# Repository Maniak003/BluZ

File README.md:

<!DOCTYPE html>
<html lang="en" data-color-mode="auto" data-light-theme="light" data-dark-theme="dark">
  <head>
    <meta charset="utf-8">
  </head>
    <body class="logged-in env-production page-responsive page-blob" style="word-wrap: break-word;">
      <p> BluZ Scintillation gamma spectrometer based on SiPM Sensl FC60035/FJ60035, Broadcom AFBR-S4N66C013, EQR15 11-6060D-S & NaI(Tl) or SrI2(Eu). Bluetooth 5.x<br>For discussion https://t.me/+mRf25RTZtPs3NTli</p>
      <a href=https://github.com/Maniak003/BluZ/releases/download/BluZ/BluZ-release.apk> Application in release </a>

    </body>
</html>

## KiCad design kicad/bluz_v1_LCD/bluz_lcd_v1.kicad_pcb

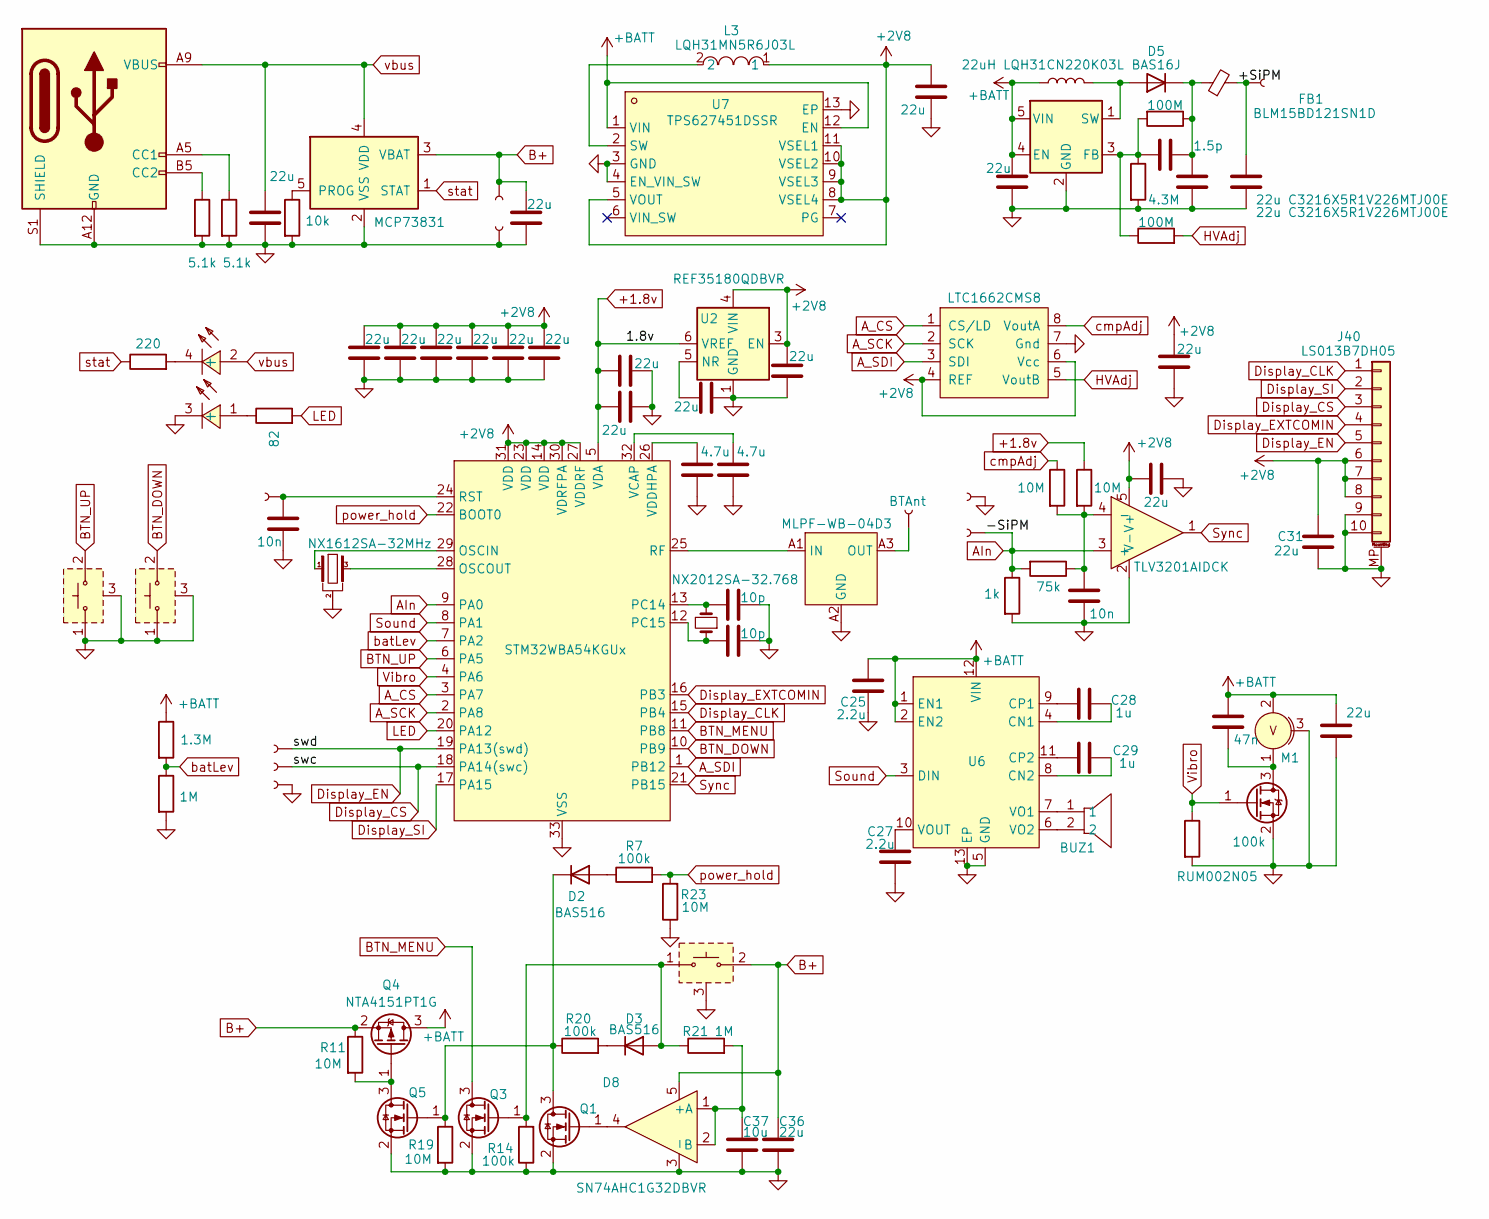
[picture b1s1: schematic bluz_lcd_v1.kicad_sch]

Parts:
BUZ1: PKMCS0909E4000-R1; BUZ-SMD_L9.0-W9.0_PKMCS0909E4000-R1; LCSC Part C910763
C1, C2, C3, C4, C5, C6, C8, C11, C13, C14, C15, C20, C23, C24, C30, C31, C32, C33, C36: 22u; C_0402_1005Metric
C7, C17: 4.7u; C_0402_1005Metric
C9: 1.5p; C_0402_1005Metric
C12, C18: 10n; C_0402_1005Metric
C16, C19: 22u C3216X5R1V226MTJ00E; C_1206_3216Metric
C21, C22: 10p; C_0201_0603Metric
C25, C27: 2.2u; C_0402_1005Metric
C26: 47n; C_0402_1005Metric
C28, C29: 1u; C_0402_1005Metric
C37: 10u; C_0402_1005Metric
D1: STM32WBA54KGUx; QFN-32-1EP_5x5mm_P0.5mm_EP3.1x3.1mm
D2, D3: BAS516; D_SOD-523
D4: LTC1662CMS8; MSOP-8_3x3mm_P0.65mm
D5: BAS16J; D_SOD-323
D6: MLPF-WB-04D3
D8: SN74AHC1G32DBVR; SOT-23-5_L3.0-W1.7-P0.95-LS2.8-BR
FB1: BLM15BD121SN1D; R_0402_1005Metric
J2, J3, J4, J5, J6, J7, J8, J10, J11: Conn; conn_mini
J9: USB_C_Receptacle_PowerOnly_6P; USB_C_Receptacle_GCT_USB4135-GF-A_6P_TopMnt_Horizontal
J12: BTAnt; conn_mini
J40: LS013B7DH05; AYF531035A
L2: 22uH LQH31CN220K03L; L_1206_3216Metric_Pad1.42x1.75mm_HandSolder
L3: LQH31MN5R6J03L; L_1206_3216Metric_Pad1.42x1.75mm_HandSolder; LCSC Part C2044369
LED1: LTST-C195KGJRKT; LED-ARRAY-SMD_0603-4P-L1.6-W1.5-BR-RD; LCSC Part C125104
M1: Z3OC1T8219731; VibroMotor
Q1, Q3, Q5: NTA4153NT1G; SOT-723
Q2: RUM002N05; SOT-723
Q4: NTA4151PT1G; SOT-416_L1.6-W0.8-P1.00-LS1.6-BR
R1: 1.3M; R_0402_1005Metric
R2, R21: 1M; R_0402_1005Metric
R3: 10k; R_0402_1005Metric
R4: 220; R_0402_1005Metric
R5: 82; R_0402_1005Metric
R6: 1k; R_0402_1005Metric
R7, R12, R14, R20: 100k; R_0402_1005Metric
R8, R9, R11, R19, R23: 10M; R_0402_1005Metric
R10: 75k; R_0402_1005Metric
R13, R16: 100M; R_0402_1005Metric
R15: 4.3M; R_0402_1005Metric
R17, R18: 5.1k; R_0402_1005Metric
SW4, SW5, SW6: SW-SMD_KMS2XXGXXX
U1: MCP73831; SOT-23-5
U2: REF35180QDBVR; SOT-23-6
U3: TLV3201AIDCK; TLV320x-SC70
U4: AP3015KTR; SOT-23-5
U6: PAM8904EGPR; W-QFN2020-12_L2.0-W2.0-P0.40-TL-EP0.9; LCSC Part C510550
U7: TPS627451DSSR; WSON-12_L3.0-W2.0-P0.5-BL-EP; LCSC Part C2866178
Y1: NX1612SA-32MHz; NX1612SA
Y2: NX2012SA-32.768; Crystal_SMD_2012-2Pin_2.0x1.2mm

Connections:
+1.8v: C8.1, C23.1, D1.5 (VDA), R9.1, U2.6 (VREF)
+2V8: C1.1, C2.1, C3.1, C5.1, C6.1, C11.1, C13.1, C14.1, C30.1, C31.1, C33.2, D1.14 (VDD), D1.23 (VDD), D1.27 (VDDRF), D1.30 (VDRFPA), D1.31 (VDD), D4.4 (REF), D4.6 (Vcc), J40.6, J40.7, J40.8, L3.1, U2.3 (EN), U2.4 (VIN), U3.5 (V+), U7.5 (VOUT), U7.8 (VSEL4), U7.9 (VSEL3), U7.10 (VSEL2), U7.11 (VSEL1)
+BATT: C15.2, C24.2, C25.1, C26.1, L2.1, M1.2, Q4.3 (D), R1.1, U4.4 (EN), U4.5 (VIN), U6.1 (EN1), U6.2 (EN2), U6.12 (VIN), U7.1 (VIN), U7.12 (EN)
/+SiPM: C19.2, FB1.2, J11.1
AIn: D1.9 (PA0), J8.1, R6.1, R10.2, U3.3 (+)
A_CS: D1.3 (PA7), D4.1 (CS/LD)
A_SCK: D1.2 (PA8), D4.2 (SCK)
A_SDI: D1.1 (PB12), D4.3 (SDI)
B+: C20.1, C36.1, D8.5 (+), J6.1, Q4.2 (S), R11.1, SW5.2, SW5.4, U1.3 (VBAT)
BTN_DOWN: D1.10 (PB9), SW6.2, SW6.4
BTN_MENU: D1.11 (PB8), Q3.3 (D)
BTN_UP: D1.6 (PA5), SW4.2, SW4.4
Display_CLK: D1.15 (PB4), J40.1
Display_CS: D1.18 (PA14(swc)), J5.1, J40.3
Display_EN: D1.19 (PA13(swd)), J4.1, J40.5
Display_EXTCOMIN: D1.16 (PB3), J40.4
Display_SI: D1.17 (PA15), J40.2
GND: C1.2, C2.2, C3.2, C4.2, C5.2, C6.2, C7.2, C8.2, C11.2, C12.2, C13.2, C14.2, C15.1, C16.1, C17.2, C18.1, C19.1, C20.2, C21.2, C22.2, C23.2, C24.1, C25.2, C27.2, C30.2, C31.2, C32.2, C33.1, C36.2, C37.2, D1.33 (VSS), D4.7 (Gnd), D6.A2 (GND), D6.B1 (GND), D6.B2 (GND), D6.B3 (GND), D8.3 (-), J3.1, J7.1, J9.A12 (GND), J9.B12 (GND), J9.S1 (SHIELD), J10.1, J40.9, J40.10, J40.MP (MountPin), LED1.3 (-), M1.3, Q1.2 (S), Q2.2 (S), Q3.2 (S), Q5.2 (S), R2.2, R3.2, R6.2, R12.2, R14.1, R15.2, R17.2, R18.2, R19.2, R23.1, SW4.1, SW4.3, SW4.5, SW5.3, SW6.1, SW6.3, SW6.5, U1.2 (VSS), U2.1 (GND), U2.2 (GND), U3.2 (V-), U4.2 (GND), U6.5 (GND), U6.13 (EP), U7.3 (GND), U7.4 (EN_VIN_SW), U7.13 (EP), Y1.2, Y1.4
HVAdj: D4.5 (VoutB), R13.2
LED: D1.20 (PA12), R5.2
unnamed: D1.29 (OSCIN), Y1.1
unnamed: D1.28 (OSCOUT), Y1.3
unnamed: C21.1, D1.13 (PC14), Y2.2
unnamed: C22.1, D1.12 (PC15), Y2.1
unnamed: D1.25 (RF), D6.A1 (IN)
unnamed: C18.2, D1.24 (RST), J2.1
unnamed: C7.1, D1.32 (VCAP)
unnamed: C17.1, D1.26 (VDDHPA)
unnamed: D2.2 (A), R7.1
unnamed: D2.1 (K), Q1.3 (D), Q5.1 (G), R19.1, R20.1
unnamed: D3.2 (A), Q3.1 (G), R14.2, R21.1, SW5.1, SW5.5
unnamed: D3.1 (K), R20.2
unnamed: D5.2 (A), L2.2, U4.1 (SW)
unnamed: C9.1, C16.2, D5.1 (K), FB1.1, R16.1
unnamed: D6.A3 (OUT), J12.1
unnamed: C37.1, D8.1 (A), D8.2 (B), R21.2
unnamed: J9.A5 (CC1), R17.1
unnamed: J9.B5 (CC2), R18.1
unnamed: LED1.1 (+), R5.1
unnamed: LED1.4 (-), R4.2
unnamed: D8.4, Q1.1 (G)
unnamed: C26.2, M1.1, Q2.3 (D)
unnamed: Q4.1 (G), Q5.3 (D), R11.2
unnamed: R3.1, U1.5 (PROG)
unnamed: C32.1, U2.5 (NR)
unnamed: C12.1, R8.2, R9.2, R10.1, U3.4 (-)
unnamed: C9.2, R13.1, R15.1, R16.2, U4.3 (FB)
unnamed: C28.2, U6.4 (CN1)
unnamed: C29.1, U6.8 (CN2)
unnamed: C28.1, U6.9 (CP1)
unnamed: C29.2, U6.11 (CP2)
unnamed: BUZ1.1, U6.7 (VO1)
unnamed: BUZ1.2, U6.6 (VO2)
unnamed: C27.1, U6.10 (VOUT)
unnamed: L3.2, U7.2 (SW)
Sound: D1.8 (PA1), U6.3 (DIN)
Sync: D1.21 (PB15), U3.1
Vibro: D1.4 (PA6), Q2.1 (G), R12.1
batLev: D1.7 (PA2), R1.2, R2.1
cmpAdj: D4.8 (VoutA), R8.1
power_hold: D1.22 (BOOT0), R7.2, R23.2
stat: R4.1, U1.1 (STAT)
vbus: C4.1, J9.A9 (VBUS), J9.B9 (VBUS), LED1.2 (+), U1.4 (VDD)

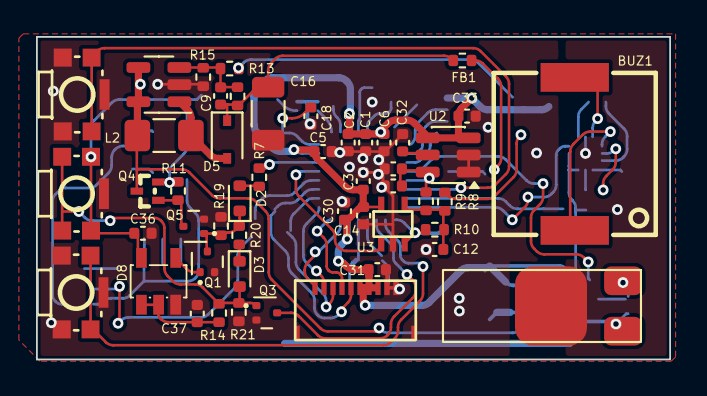
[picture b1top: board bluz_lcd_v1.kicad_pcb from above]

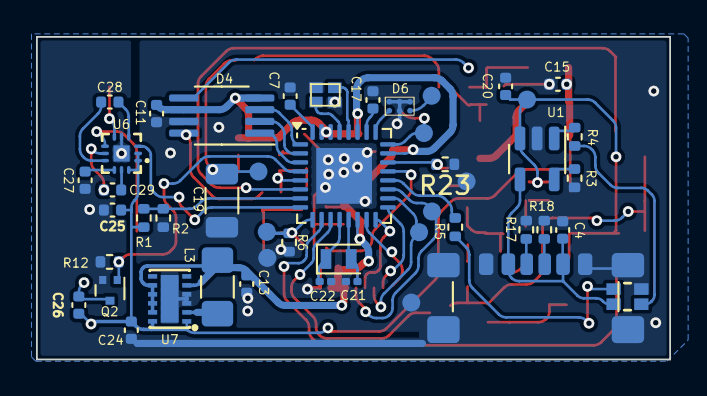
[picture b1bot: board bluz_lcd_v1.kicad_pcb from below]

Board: 2 copper layers, 35.2 x 17.9 mm, 97 parts (48 on the bottom side), 63 nets.

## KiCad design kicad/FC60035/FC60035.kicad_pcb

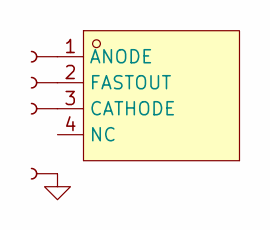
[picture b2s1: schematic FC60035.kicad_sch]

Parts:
J1, J2, J3, J4: Conn; SMD-CONN
U1: MICROFC-60035-SMT-TR; OPTO-SMD_4P-MICROFC-60035-SMT-TR; MPN MICROFC-60035-SMT-TR; LCSC Part C603293

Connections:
GND: J4.1
unnamed: J2.1, U1.1 (ANODE)
unnamed: J1.1, U1.3 (CATHODE)
unnamed: J3.1, U1.2 (FASTOUT)

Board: 2 copper layers, 5 parts (1 on the bottom side), 3 nets, no tracks yet.

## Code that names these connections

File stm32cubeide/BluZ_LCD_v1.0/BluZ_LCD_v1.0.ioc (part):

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Mcu.Name=STM32WBA54KGUx
Mcu.Package=UFQFPN32
Mcu.UserName=STM32WBA54KGUx
PA0.GPIOParameters=GPIO_Label
PA0.GPIO_Label=AIn
PA0.Mode=IN9
PA0.Signal=ADC4_IN9
PA1.GPIOParameters=GPIO_Label
PA1.GPIO_Label=SOUND
PA1.Signal=S_LPTIM2_CH2
PA12.GPIOParameters=GPIO_Label
PA12.GPIO_Label=LED
PA12.Signal=GPIO_Output
PA13\ (JTMS/SWDIO).GPIOParameters=GPIO_Label
PA13\ (JTMS/SWDIO).GPIO_Label=DISPLAY_ENABLE
PA13\ (JTMS/SWDIO).Signal=GPIO_Output
PA14\ (JTCK/SWCLK).GPIOParameters=GPIO_Label
PA14\ (JTCK/SWCLK).GPIO_Label=DISPLAY_CS
PA14\ (JTCK/SWCLK).Signal=GPIO_Output
PA15\ (JTDI).GPIOParameters=GPIO_Label
PA15\ (JTDI).GPIO_Label=DISPLAY_SI
PA15\ (JTDI).Mode=TX_Only_Simplex_Unidirect_Master
PA15\ (JTDI).Signal=SPI1_MOSI
PA2.GPIOParameters=GPIO_Label
PA2.GPIO_Label=batLev
PA2.Mode=IN7
PA2.Signal=ADC4_IN7
PA5.GPIOParameters=GPIO_Label
PA5.GPIO_Label=BTN_UP
PA5.Signal=GPIO_Input
PA6.GPIOParameters=GPIO_Label
PA6.GPIO_Label=VIBRO
PA6.Signal=GPIO_Output
PA7.GPIOParameters=GPIO_Label
PA7.GPIO_Label=A_CS
PA7.Signal=GPIO_Output
PA8.GPIOParameters=GPIO_Label
PA8.GPIO_Label=A_SCK
PA8.Signal=GPIO_Output
PB12.GPIOParameters=GPIO_Label
PB12.GPIO_Label=A_DATA
PB12.Signal=GPIO_Output
PB15.GPIOParameters=GPIO_Label,GPIO_ModeDefaultEXTI
PB15.GPIO_Label=Sync
PB15.GPIO_ModeDefaultEXTI=GPIO_MODE_IT_RISING
PB15.Signal=GPXTI15
PB3\ (JTDO/TRACESWO).GPIOParameters=GPIO_Label
PB3\ (JTDO/TRACESWO).GPIO_Label=DISPLAY_EXTCOMIN
PB3\ (JTDO/TRACESWO).Signal=S_TIM1_CH4
PB4\ (NJTRST).GPIOParameters=GPIO_Label
PB4\ (NJTRST).GPIO_Label=DISPLAY_SLC
PB4\ (NJTRST).Mode=TX_Only_Simplex_Unidirect_Master
PB4\ (NJTRST).Signal=SPI1_SCK
PB8.GPIOParameters=GPIO_Label
PB8.GPIO_Label=BTN_MENU
PB8.Signal=GPIO_Input
PB9.GPIOParameters=GPIO_Label
PB9.GPIO_Label=BTN_DOWN
PB9.Signal=GPIO_Input
PC14-OSC32_IN.Mode=LSE-External-Oscillator
PC14-OSC32_IN.Signal=RCC_OSC32_IN
PC15-OSC32_OUT.Mode=LSE-External-Oscillator
PC15-OSC32_OUT.Signal=RCC_OSC32_OUT
PH3-BOOT0.GPIOParameters=GPIO_Label
PH3-BOOT0.GPIO_Label=POWER_HOLD
PH3-BOOT0.Signal=GPIO_Output
RCC.HSESYSFreq_VALUE=16000000
RCC.HSE_VALUE=32000000
RCC.SYSCLKFreq_VALUE=16000000
board=custom

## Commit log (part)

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2025-09-04 изменено: Android/BluZ_LPM/.idea/deploymentTargetSelector.xml удалено: Android/BluZ_LPM/app/build/outputs/apk/release/app-release.apk изменено: Android/BluZ_LPM/app/src/main/AndroidManifest.xml измен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
2025-09-04 изменено: stm32cubeide/BluZ_LPM/.settings/language.settings.xml
2025-09-05 удалено: Android/BluZ_LPM/.idea/deploymentTargetSelector.xml изменено: Android/BluZ_LPM/app/build.gradle удалено: Android/BluZ_LPM/app/build/outputs/apk/release/app-release.apk изменено: Android/BluZ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
2025-09-08 изменено: stm32cubeide/BluZ_LPM/Core/Inc/main.h изменено: stm32cubeide/BluZ_LPM/Core/Src/main.c изменено: stm32cubeide/BluZ_LPM/Release/BluZ_LPM.elf
2025-09-09 удалено: Android/BluZ_LPM/app/build/outputs/apk/release/app-release.apk
2025-09-16 изменено: stm32cubeide/BluZ_LPM/.settings/language.settings.xml изменено: stm32cubeide/BluZ_LPM/Core/Inc/main.h изменено: stm32cubeide/BluZ_LPM/Core/Src/main.c изменено: stm32cubeide/BluZ_LPM/Release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
2025-09-17 новый файл: FreeCAD/Chassis.stl новый файл: FreeCAD/Cover.stl новый файл: FreeCAD/Detector cover.stl
2025-09-21 изменено: Android/BluZ_LPM/.idea/deploymentTargetSelector.xml новый файл: Documents/comparator_delay.png новый файл: Documents/comparator_raise.png новый файл: Documents/opa_delay.png новый файл: Doc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
2025-09-23 изменено: Android/BluZ_LPM/app/src/main/java/ru/starline/bluz/MainActivity.kt изменено: Android/BluZ_LPM/app/src/main/java/ru/starline/bluz/NumberFragment.kt изменено: Android/BluZ_LPM/app/src/main/j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
2025-09-25 изменено: Android/BluZ_LPM/app/src/main/java/ru/starline/bluz/NumberFragment.kt изменено: Android/BluZ_LPM/app/src/main/java/ru/starline/bluz/data/dao/DosimeterDao.kt
2025-10-07 изменено: Android/BluZ_LPM/app/build.gradle изменено: Android/BluZ_LPM/app/src/main/AndroidManifest.xml изменено: Android/BluZ_LPM/app/src/main/java/ru/starline/bluz/MainActivity.kt новый файл: Andro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
2025-10-09 изменено: Android/BluZ_LPM/app/src/main/AndroidManifest.xml изменено: Android/BluZ_LPM/app/src/main/java/ru/starline/bluz/BluetoothInterface.kt изменено: Android/BluZ_LPM/app/src/main/java/ru/starlin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
2025-10-13 удалено: kicad/bluz_v1_typec/bluz_v1-backups/bluz_v1-2024-12-26_190152.zip удалено: kicad/bluz_v1_typec/bluz_v1-backups/bluz_v1-2024-12-27_152005.zip удалено: kicad/bluz_v1_typec/bluz_v1-backups/bluz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
2025-10-14 новый файл: Android/BluZ_LPM/app/src/main/java/ru/starline/bluz/utils/Task.kt
2025-10-17 изменено: Android/BluZ_LPM/app/src/main/java/ru/starline/bluz/NumberFragment.kt изменено: Android/BluZ_LPM/app/src/main/java/ru/starline/bluz/bgService.kt
2025-10-20 изменено: README.md
2025-10-21 удалено: kicad/bluz_v1_typec/bluz_v1-backups/bluz_v1-2025-03-25_124207.zip удалено: kicad/bluz_v1_typec/bluz_v1-backups/bluz_v1-2025-03-25_145630.zip изменено: kicad/bluz_v1_typec/bluz_v1.kicad_pcb и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
2025-11-03 новый файл: FreeCAD/BluZ_case_10x40_type_c.FCStd новый файл: FreeCAD/BluZ_cover_10x40_type-c.FCStd изменено: stm32cubeide/BluZ_LPM/Core/Src/app_entry.c изменено: stm32cubeide/BluZ_LPM/Core/Src/main.c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
2025-11-05 удалено: kicad/bluz_v1_typec/bluz_v1-backups/bluz_v1-2025-03-25_184904.zip удалено: kicad/bluz_v1_typec/bluz_v1-backups/bluz_v1-2025-05-30_173628.zip удалено: kicad/bluz_v1_typec/bluz_v1-backups/bluz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
2025-11-13 изменено: Android/BluZ_LPM/BluZ/src/main/java/ru/starline/bluz/BluetoothInterface.kt изменено: Android/BluZ_LPM/BluZ/src/main/java/ru/starline/bluz/NumberFragment.kt изменено: Android/BluZ_LPM/BluZ/s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
2025-11-14 изменено: Android/BluZ_LPM/BluZ/src/main/java/ru/starline/bluz/drawDozimeter.kt изменено: Android/BluZ_LPM/BluZ/src/main/java/ru/starline/bluz/drawExmple.kt изменено: Android/BluZ_LPM/BluZ/src/main/j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
2025-11-15 изменено: stm32cubeide/BluZ_LPM/.mxproject изменено: stm32cubeide/BluZ_LPM/BluZ_LPM.ioc изменено: stm32cubeide/BluZ_LPM/Core/Src/main.c изменено: stm32cubeide/BluZ_LPM/Release/BluZ_LPM.elf
2025-11-16 изменено: Android/BluZ_LPM/BluZ/src/main/java/ru/starline/bluz/NumberFragment.kt
2025-11-17 изменено: stm32cubeide/BluZ_LPM/.mxproject изменено: stm32cubeide/BluZ_LPM/Core/Inc/main.h изменено: stm32cubeide/BluZ_LPM/Release/BluZ_LPM.elf
2025-11-17 изменено: stm32cubeide/BluZ_LPM/Release/BluZ_LPM.elf изменено: stm32cubeide/BluZ_LPM/STM32_WPAN/App/app_ble.c изменено: stm32cubeide/BluZ_LPM/STM32_WPAN/App/bluz_app.c
2025-11-18 изменено: FreeCAD/BluZ_cover_10x10.FCStd изменено: FreeCAD/BluZ_cover_10x10.stl изменено: FreeCAD/BluZ_cover_10x40_type-c.FCStd
2025-11-18 изменено: Android/BluZ_LPM/BluZ/src/main/java/ru/starline/bluz/NumberFragment.kt изменено: Android/BluZ_LPM/BluZ/src/main/res/layout/setup_layout.xml изменено: Android/BluZ_LPM/BluZ/src/main/res/valu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
2025-11-19 новый файл: stm32cubeide/BluZ_LPM/Release/BluZ_LPM.elf
2025-11-19 изменено: stm32cubeide/BluZ_LPM/Core/Src/main.c изменено: stm32cubeide/BluZ_LPM/Core/Src/stm32wbaxx_it.c изменено: stm32cubeide/BluZ_LPM/Release/BluZ_LPM.elf
2025-11-21 изменено: Android/BluZ_LPM/BluZ/src/main/AndroidManifest.xml изменено: Android/BluZ_LPM/BluZ/src/main/java/ru/starline/bluz/BluetoothInterface.kt изменено: Android/BluZ_LPM/BluZ/src/main/java/ru/star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
2025-11-22 изменено: Android/BluZ_LPM/BluZ/src/main/java/ru/starline/bluz/BluetoothInterface.kt изменено: kicad/bluz_v1_typec/bluz_v1.kicad_prl
2025-11-24 изменено: stm32cubeide/BluZ_LPM/Core/Inc/main.h изменено: stm32cubeide/BluZ_LPM/Core/Src/main.c изменено: stm32cubeide/BluZ_LPM/Core/Src/rw_FLASH.c изменено: stm32cubeide/BluZ_LPM/Core/Src/stm32wbaxx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
2025-12-01 изменено: FreeCAD/BluZ_case_10x40_type_c.FCStd новый файл: FreeCAD/BluZ_case_2_10x40_type-c.FCStd новый файл: FreeCAD/BluZ_case_2_10x40_type-c.stl изменено: FreeCAD/BluZ_cover_10x40_type-c.FCStd изме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
2025-12-14 изменено: FreeCAD/BluZ_case_2_10x40_type-c.FCStd изменено: FreeCAD/BluZ_case_2_10x40_type-c.stl изменено: FreeCAD/BluZ_cover_2_10x10_type-c.FCStd изменено: FreeCAD/BluZ_cover_2_10x10_type-c.stl измен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
2025-12-18 изменено: Android/BluZ_LPM/BluZ/src/main/java/ru/starline/bluz/MainActivity.kt изменено: Android/BluZ_LPM/BluZ/src/main/java/ru/starline/bluz/NumberFragment.kt изменено: Android/BluZ_LPM/BluZ/src/mai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
2025-12-21 изменено: stm32cubeide/BluZ_LPM/Core/Inc/main.h изменено: stm32cubeide/BluZ_LPM/Release/BluZ_LPM.elf
2025-12-26 изменено: Android/BluZ_LPM/BluZ/src/main/java/ru/starline/bluz/MainActivity.kt изменено: Android/BluZ_LPM/BluZ/src/main/java/ru/starline/bluz/drawLogs.kt изменено: Android/BluZ_LPM/BluZ/src/main/java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
2025-12-26 изменено: Documents/Screenshot_20251116-123809.jpg
2026-01-26 удалено: kicad/bluz_v1_typec/bluz_v1-backups/bluz_v1-2025-08-04_170630.zip удалено: kicad/bluz_v1_typec/bluz_v1-backups/bluz_v1-2025-08-04_172315.zip изменено: kicad/bluz_v1_typec/bluz_v1.kicad_prl и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
2026-01-27 изменено: kicad/bluz_v1_typec/bluz_v1.kicad_pcb изменено: kicad/bluz_v1_typec/bluz_v1.kicad_prl
2026-01-28 удалено: kicad/bluz_v1_typec/bluz_v1-backups/bluz_v1-2025-08-04_173346.zip изменено: kicad/bluz_v1_typec/bluz_v1.kicad_pcb изменено: kicad/bluz_v1_typec/bluz_v1.kicad_sch изменено: kicad/bluz_v1_type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
2026-01-30 изменено: Android/BluZ_LPM/BluZ/src/main/java/ru/starline/bluz/MLEM.kt изменено: Android/BluZ_LPM/BluZ/src/main/java/ru/starline/bluz/MainActivity.kt изменено: Android/BluZ_LPM/BluZ/src/main/java/ru/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
2026-02-06 изменено: Android/BluZ_LPM/BluZ/src/main/java/ru/starline/bluz/MLEM.kt изменено: Android/BluZ_LPM/BluZ/src/main/java/ru/starline/bluz/NumberFragment.kt изменено: Android/BluZ_LPM/BluZ/src/main/java/r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
2026-02-10 изменено: Android/BluZ_LPM/BluZ/src/main/java/ru/starline/bluz/MLEM.kt изменено: Android/BluZ_LPM/BluZ/src/main/java/ru/starline/bluz/NumberFragment.kt
2026-02-13 изменено: Android/BluZ_LPM/BluZ/src/main/AndroidManifest.xml изменено: Android/BluZ_LPM/BluZ/src/main/java/ru/starline/bluz/BluetoothInterface.kt изменено: Android/BluZ_LPM/BluZ/src/main/java/ru/star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
2026-02-16 изменено: kicad/bluz_v2_typec/bluz_v1.kicad_pcb изменено: kicad/bluz_v2_typec/bluz_v1.kicad_prl изменено: kicad/bluz_v2_typec/bluz_v1.kicad_pro изменено: kicad/bluz_v2_typec/bluz_v1.kicad_sch
2026-02-18 изменено: Android/BluZ_LPM/BluZ/src/main/java/ru/starline/bluz/NumberFragment.kt изменено: Android/BluZ_LPM/BluZ/src/main/java/ru/starline/bluz/drawSpecter.kt изменено: Android/BluZ_LPM/BluZ/src/main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
2026-02-20 удалено: kicad/bluz_v2_typec/bluz_v1-backups/bluz_v1-2025-11-02_134433.zip удалено: kicad/bluz_v2_typec/bluz_v1-backups/bluz_v1-2025-11-02_135440.zip изменено: kicad/bluz_v2_typec/bluz_v1.kicad_pcb и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
2026-02-23 изменено: stm32cubeide/BluZ_LPM/.project удалено: stm32cubeide/BluZ_LPM/BluZ_LPM.ioc изменено: stm32cubeide/BluZ_LPM/programm.sh
2026-03-06 изменено: kicad/bluz_v1_typec/bluz_v1.kicad_prl
2026-03-15 изменено: stm32cubeide/BluZ_LPM/.mxproject изменено: stm32cubeide/BluZ_LPM/BluZ_LPM_v1.ioc
2026-04-02 изменено: Android/BluZ_LPM/BluZ/src/main/java/ru/starline/bluz/NumberFragment.kt изменено: Android/BluZ_LPM/BluZ/src/main/java/ru/starline/bluz/drawCursor.kt изменено: stm32cubeide/BluZ_LPM_v2/.setti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
2026-04-10 изменено: Android/BluZ_LPM/BluZ/src/main/AndroidManifest.xml изменено: Android/BluZ_LPM/BluZ/src/main/java/ru/starline/bluz/NumberFragment.kt изменено: Android/BluZ_LPM/BluZ/src/main/java/ru/starline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
2026-04-13 новый файл: Documents/setup_screen.png
2026-04-17 удалено: kicad/bluz_v2_typec/bluz_v1-backups/bluz_v1-2026-01-27_180557.zip удалено: kicad/bluz_v2_typec/bluz_v1-backups/bluz_v1-2026-01-27_191409.zip удалено: kicad/bluz_v2_typec/bluz_v1-backups/bluz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
2026-04-29 изменено: Android/BluZ_LPM/BluZ/src/main/java/ru/starline/bluz/BluetoothInterface.kt изменено: Android/BluZ_LPM/BluZ/src/main/java/ru/starline/bluz/MainActivity.kt изменено: Android/BluZ_LPM/BluZ/src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
2026-05-08 удалено: Android/BluZ_LPM/BluZ/src/main/java/ru/starline/bluz/MLEM.kt изменено: Android/BluZ_LPM/BluZ/src/main/java/ru/starline/bluz/MainActivity.kt изменено: Android/BluZ_LPM/BluZ/src/main/java/ru/s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
2026-05-09 изменено: kicad/bluz_v2_typec/bluz_v1.kicad_prl изменено: kicad/bluz_v2_typec/bluz_v1.kicad_sch
2026-05-12 изменено: Documents/EnergComp/Geant4/NaI_10x10/build/NaI_response_h1_Edep.csv изменено: Documents/EnergComp/Geant4/NaI_10x10/build/exec.txt изменено: Documents/EnergComp/Geant4/NaI_10x10/build/genera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
2026-05-13 новый файл: Documents/EnergComp/Geant4/CsI_10x10x30/CMakeLists.txt новый файл: Documents/EnergComp/Geant4/CsI_10x10x30/GNUmakefile новый файл: Documents/EnergComp/Geant4/CsI_10x10x30/History новый фа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
2026-05-22 изменено: Android/BluZ_LPM/BluZ/src/main/java/ru/starline/bluz/calculateDose.kt изменено: Android/BluZ_LPM/BluZ/src/main/java/ru/starline/bluz/drawSpecter.kt изменено: Android/BluZ_LPM/BluZ/src/main/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
2026-05-22 новый файл: Documents/EnergComp/Geant4/NaI_10x10/build/generate_matrix_parallel.sh
2026-05-31 изменено: kicad/bluz_v2_typec/bluz_v1.kicad_pcb изменено: kicad/bluz_v2_typec/bluz_v1.kicad_sch изменено: kicad/bluz_v2_typec/fp-info-cache
2026-06-01 BluZv2
2026-06-02 изменено: Android/BluZ_v2/BluZ/Android/BluZ_LPM/.idea/vcs.xml изменено: Android/BluZ_v2/BluZ/Android/BluZ_LPM/BluZ/src/main/java/ru/starline/bluz/AutoCalibrationController.kt изменено: Android/BluZ_v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
2026-06-06 новый файл: FreeCAD/BluZ_case_3_type-c.FCStd новый файл: FreeCAD/BluZ_case_3_type-c.stl новый файл: FreeCAD/BluZ_cover_2_10x10x40_type-c.FCStd новый файл: FreeCAD/BluZ_cover_2_10x10x40_type-c.stl
2026-06-10 изменено: Android/BluZ_v2/BluZ/Android/BluZ_LPM/BluZ/src/main/java/ru/starline/bluz/MainActivity.kt изменено: Android/BluZ_v2/BluZ/Android/BluZ_LPM/BluZ/src/main/java/ru/starline/bluz/NumberAdapter.k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
2026-06-12 новый файл: "Documents/\320\232\320\276\320\275\321\206\320\265\320\275\321\202\321\200\320\270\321\200\320\276\320\262\320\260\320\275\320\270\320\265 \320\276\320\261\321\200\320\260\320\267\321\20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
2026-06-14 изменено: Android/BluZ_LPM/.idea/misc.xml удалено: Android/BluZ_v2/BluZ/Android/BluZ_LPM/.idea/deploymentTargetSelector.xml изменено: Android/BluZ_v2/BluZ/Android/BluZ_LPM/.idea/misc.xml изменено: An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
2026-06-16 изменено: kicad/bluz_v2_typec/bom/ibom.html
